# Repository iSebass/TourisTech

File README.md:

# TuristTech

## Introducción

En el contexto de un mundo cada vez más consciente de la importancia de la sostenibilidad y la conservación del medio ambiente, surge un proyecto visionario que busca revolucionar la industria del ecoturismo en Colombia. En este proyecto encontrarás la implementación de una red IoT para monitorear y controlar dispositivos en un ecotel, uniendo la tecnología con la conservación del entorno natural.

## Metodología 

En el marco de este proyecto, la metodología establece las fases fundamentales desde la planificación inicial hasta la culminación del proceso, garantizando una gestión eficaz y coherente en cada etapa. Esta metodología se sustenta en la colaboración interdisciplinaria entre especialistas en tecnología, turismo y conservación, integrando además prácticas ágiles y flexibles para ajustarse a las exigencias y dinámicas del entorno en constante cambio. 

1. **Implementación de Alexa**: La implementación de Alexa marca un avance significativo en el proyecto, al ofrecer una interacción innovadora para los usuarios del ecotel. Este punto de la metodología se enfoca en dos etapas cruciales:
   
    1. **Configuración inicial de Alexa**: Se trata de preparar y conectar los dispositivos necesarios, configurar la aplicación y la cuenta asociada. Esta etapa establece la base tecnológica esencial para la interacción con el asistente de voz. Para la configuración inicial de Alexa, se deben seguir los siguientes pasos:
   
       1. **Descargar la aplicación de Alexa:**
          - Si estás usando un dispositivo Android, descarga la aplicación de Alexa desde [Google Play Store](https://play.google.com/store/apps/details?id=com.amazon.dee.app&pcampaignid=web_share "Google Play Store").
          - Si utilizas un dispositivo Apple, encuentra la aplicación en [App Store](https://apps.apple.com/ni/app/amazon-alexa/id944011620 "App Store").
       
       2. **Vincular o registrar una cuenta de Amazon:**
          - Si aún no tienes una cuenta de Amazon, regístrate.
          - Inicia sesión con tu cuenta de Amazon en la aplicación de Alexa.
       
       3. **Instalar una Skill:**
          - Dentro de la aplicación de Alexa, dirígete a la sección de "Skills" y selecciona "Buscar Skills".
          - Busca la Skill "Ben Hardill - Node-RED" o utiliza este [enlace directo](https://www.amazon.com/Ben-Hardill-Node-RED/dp/B01N0D97FZ) para instalarla.
          - Una vez instalada, sigue las instrucciones para habilitar la Skill y conceder los permisos necesarios para vincular Alexa con Node-RED.
 
   2. **Integración de Alexa con Node-RED**: Aquí, se exploran los pasos para conectar Alexa a Node-RED, una plataforma que facilita la automatización y el control de dispositivos IoT. Se configuran los nodos correspondientes para una comunicación efectiva entre ambos sistemas.

Estas etapas son fundamentales para aprovechar al máximo la implementación de Alexa, mejorando la experiencia del ecoturismo. Una cuidadosa planificación y ejecución en estas áreas sientan las bases para una integración exitosa del asistente de voz en el entorno del ecotel.

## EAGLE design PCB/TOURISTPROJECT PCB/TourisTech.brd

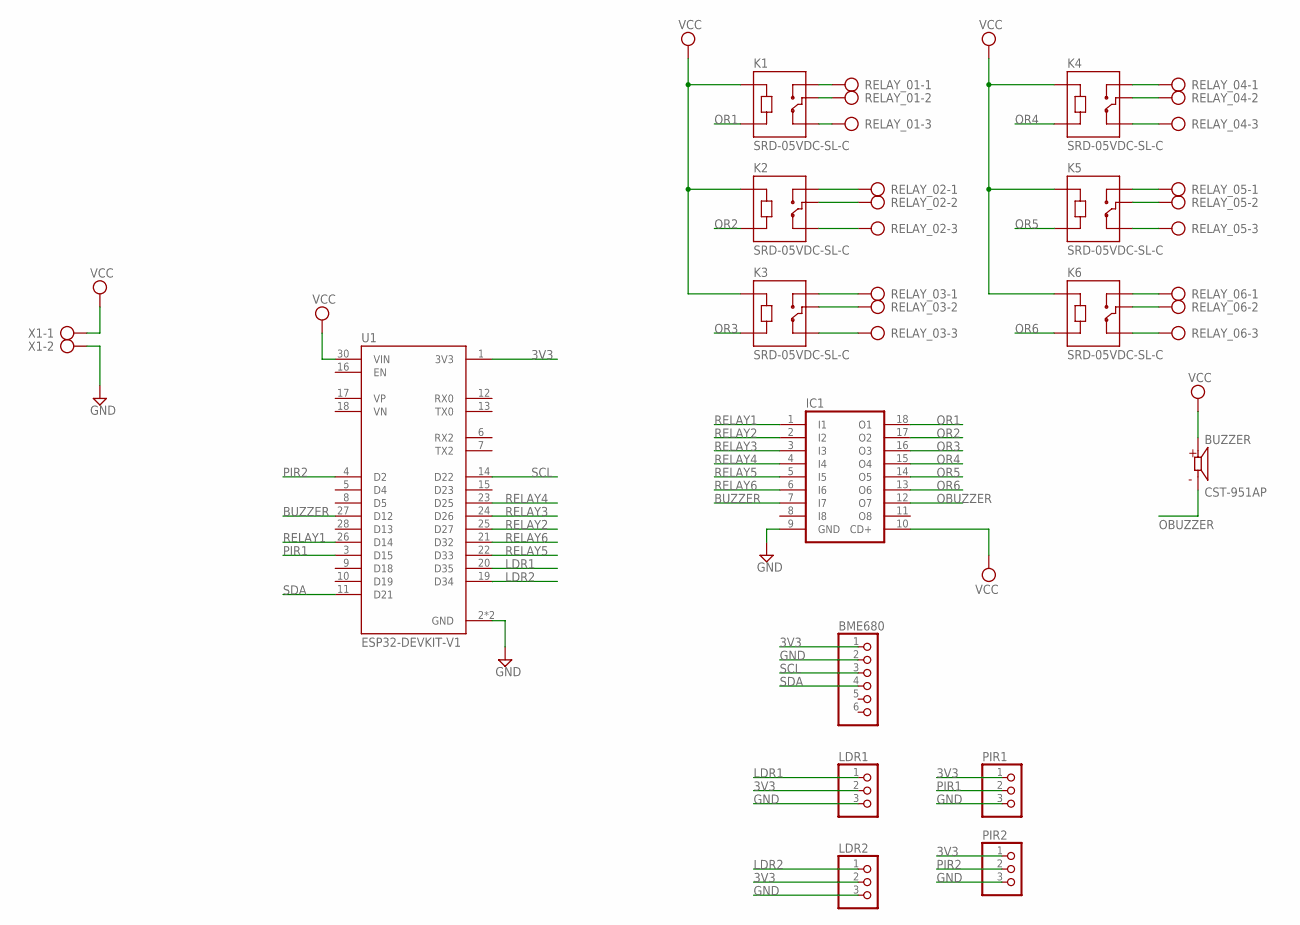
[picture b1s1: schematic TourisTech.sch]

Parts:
BME680: PINHD-1X6; 1X06
BUZZER: CST-951AP; CUI_CST-951AP
IC1: ULN2803A; DIL18
K1, K2, K3, K4, K5, K6: SRD-05VDC-SL-C; RELAY_SRD-05VDC-SL-C
LDR1, LDR2: PINHD-1X3; 1X03
PIR1, PIR2: PINHD-1X3; 1X03
RELAY_01, RELAY_02, RELAY_03, RELAY_04, RELAY_05, RELAY_06: AK300/3
U1: ESP32-DEVKIT-V1; MODULE_ESP32_DEVKIT_V1
X1: AK300/2

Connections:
3V3: BME680.1, LDR1.2, LDR2.2, PIR1.1, PIR2.1, U1.1 (3V3)
BUZZER: IC1.7 (I7), U1.27 (D12)
GND: BME680.2, IC1.9 (GND), LDR1.3, LDR2.3, PIR1.3, PIR2.3, U1.2 (GND), U1.29 (GND), X1.2
LDR1: LDR1.1, U1.20 (D35)
LDR2: LDR2.1, U1.19 (D34)
unnamed: K1.NO, RELAY_01.1
unnamed: K1.COM, RELAY_01.2
unnamed: K1.NC, RELAY_01.3
unnamed: K2.NO, RELAY_02.1
unnamed: K2.COM, RELAY_02.2
unnamed: K2.NC, RELAY_02.3
unnamed: K3.NO, RELAY_03.1
unnamed: K3.COM, RELAY_03.2
unnamed: K3.NC, RELAY_03.3
unnamed: K4.NO, RELAY_04.1
unnamed: K4.COM, RELAY_04.2
unnamed: K4.NC, RELAY_04.3
unnamed: K5.NO, RELAY_05.1
unnamed: K5.COM, RELAY_05.2
unnamed: K5.NC, RELAY_05.3
unnamed: K6.NO, RELAY_06.1
unnamed: K6.COM, RELAY_06.2
unnamed: K6.NC, RELAY_06.3
OBUZZER: BUZZER.M, IC1.12 (O7)
OR1: IC1.18 (O1), K1.A2
OR2: IC1.17 (O2), K2.A2
OR3: IC1.16 (O3), K3.A2
OR4: IC1.15 (O4), K4.A2
OR5: IC1.14 (O5), K5.A2
OR6: IC1.13 (O6), K6.A2
PIR1: PIR1.2, U1.3 (D15)
PIR2: PIR2.2, U1.4 (D2)
RELAY1: IC1.1 (I1), U1.26 (D14)
RELAY2: IC1.2 (I2), U1.25 (D27)
RELAY3: IC1.3 (I3), U1.24 (D26)
RELAY4: IC1.4 (I4), U1.23 (D25)
RELAY5: IC1.5 (I5), U1.22 (D33)
RELAY6: IC1.6 (I6), U1.21 (D32)
SCL: BME680.3, U1.14 (D22)
SDA: BME680.4, U1.11 (D21)
VCC: BUZZER.P, IC1.10 (CD+), K1.A1, K2.A1, K3.A1, K4.A1, K5.A1, K6.A1, U1.30 (VIN), X1.1

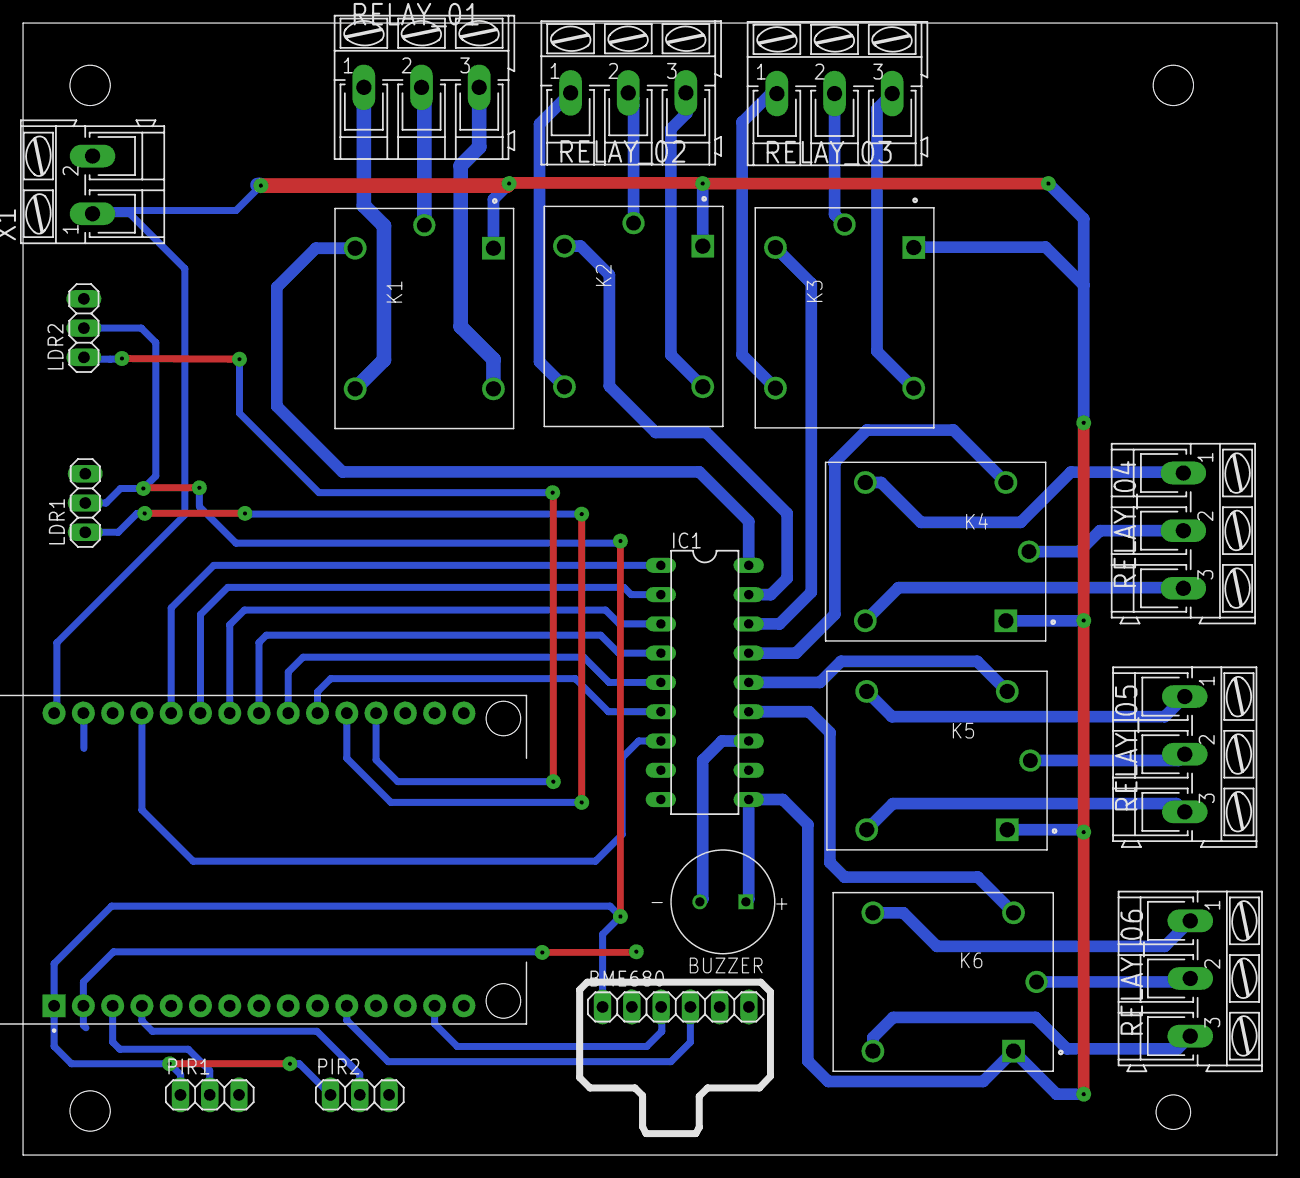
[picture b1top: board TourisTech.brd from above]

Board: 2 copper layers, 108.8 x 98.2 mm, 21 parts (0 on the bottom side), 41 nets.

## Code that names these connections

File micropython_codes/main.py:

from machine import Pin, I2C
from time import sleep
from bme680 import *
from TuristProject import *
from ESP_Connection import *

list_relay_connection = [14,27,26,25,33,32]

RELAY1=0
RELAY2=1
RELAY3=2
RELAY4=3
RELAY5=4
RELAY6=5

MY_SSID  = getSSID()
MY_PASS  = getPASS()
MY_TOKEN = getToken()

time_to_send = 3000


def run():
    global time_to_send
    counter_sample = 0
    wifi = ESP_Connect(SSID=MY_SSID, PASS= MY_PASS)
    wifi.connect_ubidots(MY_TOKEN)
    
    i2c = I2C(1, scl=Pin(22), sda=Pin(21), freq=100000)
    bme = BME680_I2C(i2c=i2c)
    ldr_interior = LDR(pinldr=34)
    ldr_exterior = LDR(pinldr=35)
    pirA = PIR(pinpir=15)
    pirB = PIR(pinpir=2)
    relays = RELAY(list_relays =list_relay_connection )
    buzzer = BUZZER(pin_buzzer=12)
    
    buzzer.play_buzzer(5)
    relays.set_relay(RELAY1)
    relays.set_relay(RELAY4)
    while True:
        
        
        
        ldr_int_val = ldr_interior.get_ldr_Value()
        ldr_ext_val = ldr_exterior.get_ldr_Value()
        
        pirA_val = pirA.get_pir_Value()
        pirB_val = pirB.get_pir_Value()
        
        temp = bme.temperature
        hum  = bme.humidity
        pres = bme.pressure
        gas  = bme.gas
        
        if counter_sample == time_to_send:
            wifi.publish_ubidots(typeVar="Temperature",value=temp,context="AulaSteam")
            wifi.publish_ubidots(typeVar="Humidity",value=hum,context="AulaSteam")
            wifi.publish_ubidots(typeVar="Pressure",value=pres,context="AulaSteam")
            wifi.publish_ubidots(typeVar="Gas",value=gas,context="AulaSteam")
            
            counter_sample = 0
        
        print("Temp: ",temp)
        print("Hum: ",hum)
        print("Pres: ",pres)
        print("Gas: ",gas)
        print("")
        print("LDR INT: ",ldr_int_val)
        print("LDR EXT: ",ldr_ext_val)
        print("")
        print("PIR A: ",pirA_val)
        print("PIR B: ",pirB_val)
        print("")
        counter_sample += 1
        sleep(0.3)
        
        


if __name__=="__main__":
    run()

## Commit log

2023-08-20 Se agregan primeros codigos del proyecto
2023-08-22 Se agregan archivos de PCB y codigos de Python FUncionando@
2023-08-22 Se actualiza Boot.py
2023-08-22 Se actualiza codigo con Credenciales de Ubidots Julian
2024-02-19 README.md
2024-03-20 PCB - PLACA MADRE
2024-03-20 PlacaOtraVez
2024-04-03 Ultima PCB
    PCB Final
2024-04-06 Nueva version del esquematico de la placa
    La unica modificacion que hice fue organizar un poco mejor el esquematico, osea el archivo .kicad_sch
2024-04-06 Version de frabricacion 01
2024-04-12 Se agregan modelos 3D
2024-04-12 Se agrega PCB del modulo 01
